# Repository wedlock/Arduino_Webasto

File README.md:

# Arduino_Webasto

Projekt sterownika do Webasto oparty na adruino ( w tym przyopadku Adruino nano ). Do działania całości niezbędne są dwa termometry ( DS18B20 ) do odczytu temperatury spalin i cieczy w układzie oraz wyświetlacz LCD 2x16 linii , 1 przycisk monostabilny, kilka rezystorów, MOSFETY i diody LED  ( wszystkie elementy są wymienione w schemacie ). Sterownik ustawiony jest na maksymalną temperaturę 70 stopni .

Do projektu dołączam pliki EAGLE i PDF niezbędne do wykonania płytki.

Krótka instrukcja działania :

Gdy sterownik znajduje się w stanie IDLE jednoktorne wciśnięcie przycisku powoduje rozpoczęcie sekwencji startowej. Na ekranie wyświetla się napis BURNING UP. Ponowne wciśnięcie przycisku w każdym momencie gdy sterownik jest w trybie BURNING UP, WORKING albo SLEEP powoduje wygaszenie pieca. Przytrzymanie przycisku 2 sek powoduje natychmiastowe zatrzymanie i reset programu.

Podczas pracy sterownik cały czas sprawdza temp. spalin i wody i gdy wykryje nieprawidłowości wyłącza układ. Mi osobiście przez całą zimę nie wyłączył się awaryjnie ani razu. Dla bezpieczeństwa wbudowałem watchdoga, który co kilka milisekund sprawdza czy arduino się zawiesiło, a jeśli tak to resetuje cału układ i wygasza się on bezpiecznie.

Stany sterownika:
1. IDLE oczekuje na włączenie ( sprawdzanie temp. cieczy ciągle włączone i ewentualnie włączy się pompa wody gdy temperatura wzrośnie )
2. BURNING UP rozpalanie pieca. Odbywa się to etapami :
  - przedmuchanie komory spalania celem pozbycia się oparów ropy
  - którkie pomowanie paliwa żeby rozsączyło się na palniku i odczekanie kulku sekund
  - włączenie świecy żarowej
  - gdy nastąpi wzrost temp. wody o 3 stopnie lub temp. wody o 2 stopnie piec przechodzi w tryb działania WORK
3. WORK - normalna praca pieca. Przy temp wody 20 stopni pompa wody jest włączana na 1/2 mocy. Zapobiega to gotowaniu się wody na powierzchni webasta. Po ogrzaniu się wody do 30 stopni sterownik urychamia się na 100% mocy. Gdy temp wody dojdzie do 70 stopni piec usypia się i czeka aż woda ostygnie do 65 stopni po czym znowy się uruchamia
4. BURN OFF wygaszanmie pieca. Nie jest podawane paliwa a wiatrak zwalnia. Zapobiega to cofaniu się płomienia. Gdy temp. spalin i wody przez dłuższą chwilę nie wzrasta, piec wyłącza się.

Na płytce zapomniałem dodać pinów do wlutowania przycisku ( ups. ) ale bez problemu da się to przylutować bezpośrednio do płytki. Są to przewody sygnałowe i ich średnica może być nawet i 0,5mm

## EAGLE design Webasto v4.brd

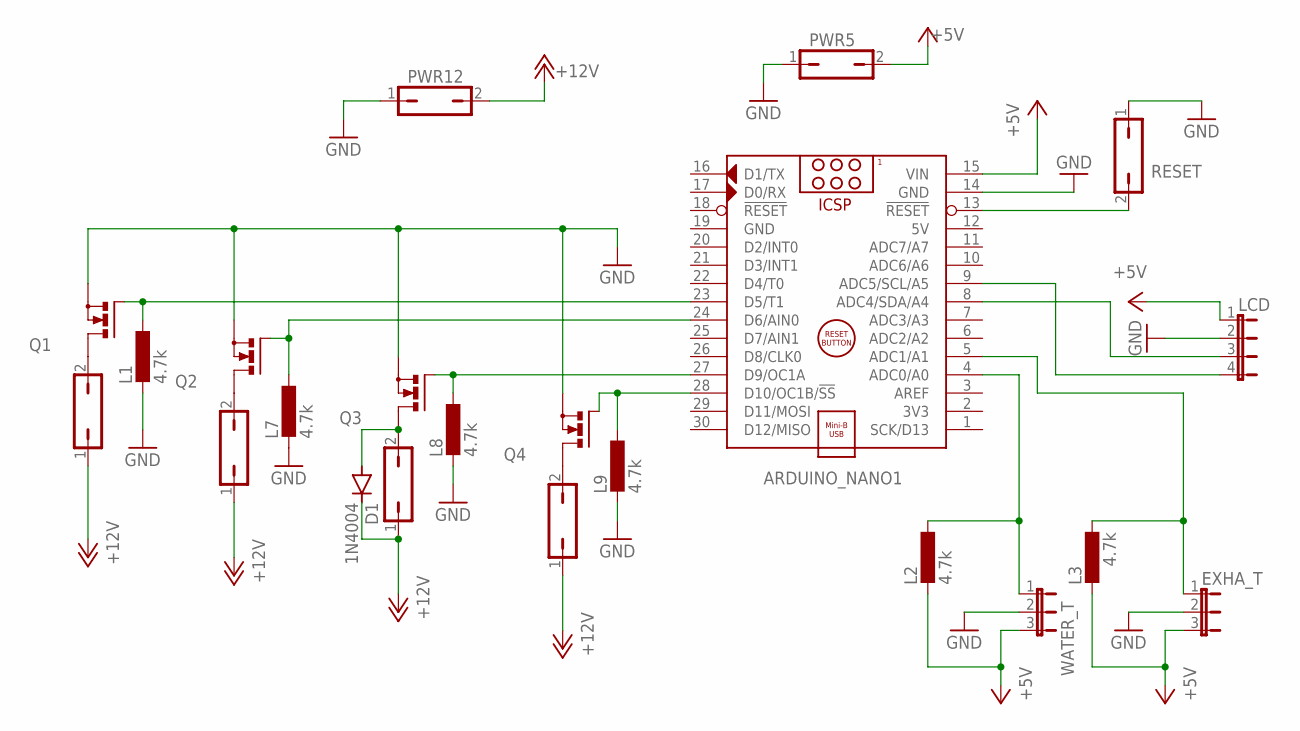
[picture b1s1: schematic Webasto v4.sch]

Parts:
ARDUINO_NANO1: ARDUINO_NANO
D1: 1N4004; DO41-10
EXHA_T: JP2E; JP2
FAN: 794681-2; JP1
FUEL: 794681-2; JP1
GLOW: 794681-2; JP1
L1, L2, L3, L7, L8, L9: 4.7k; 0204/7
LCD: JP4E; JP4
PWR5, PWR12: JP1Q; JP1
Q1, Q2, Q3, Q4: IRLB8721; TO220BV
RESET: power; JP1
WATER: 794681-2; JP1
WATER_T: JP2E; JP2

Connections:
5V: ARDUINO_NANO1.12 (5V)
+5V: ARDUINO_NANO1.15 (VIN), EXHA_T.3, L2.2, L3.2, LCD.1, PWR5.2, WATER_T.3
+12V: D1.C, FAN.1, FUEL.1, GLOW.1, PWR12.2, WATER.1
GND: ARDUINO_NANO1.14 (GND), ARDUINO_NANO1.19 (GND), EXHA_T.2, L1.2, L7.2, L8.2, L9.2, LCD.2, PWR5.1, PWR12.1, Q1.S, Q2.S, Q3.S, Q4.S, RESET.1, WATER_T.2
unnamed: ARDUINO_NANO1.23 (D5/T1), L1.1, Q1.G
unnamed: FUEL.2, Q1.D
unnamed: ARDUINO_NANO1.24 (D6/AIN0), L7.1, Q2.G
unnamed: GLOW.2, Q2.D
unnamed: ARDUINO_NANO1.27 (D9/OC1A), L8.1, Q3.G
unnamed: D1.A, FAN.2, Q3.D
unnamed: ARDUINO_NANO1.28 (D10/OC1B/!SS), L9.1, Q4.G
unnamed: Q4.D, WATER.2
unnamed: ARDUINO_NANO1.8 (ADC4/SDA/A4), LCD.3
unnamed: ARDUINO_NANO1.9 (ADC5/SCL/A5), LCD.4
unnamed: ARDUINO_NANO1.5 (ADC1/A1), EXHA_T.1, L3.1
unnamed: ARDUINO_NANO1.4 (ADC0/A0), L2.1, WATER_T.1
RESET: ARDUINO_NANO1.13 (!RESET), RESET.2

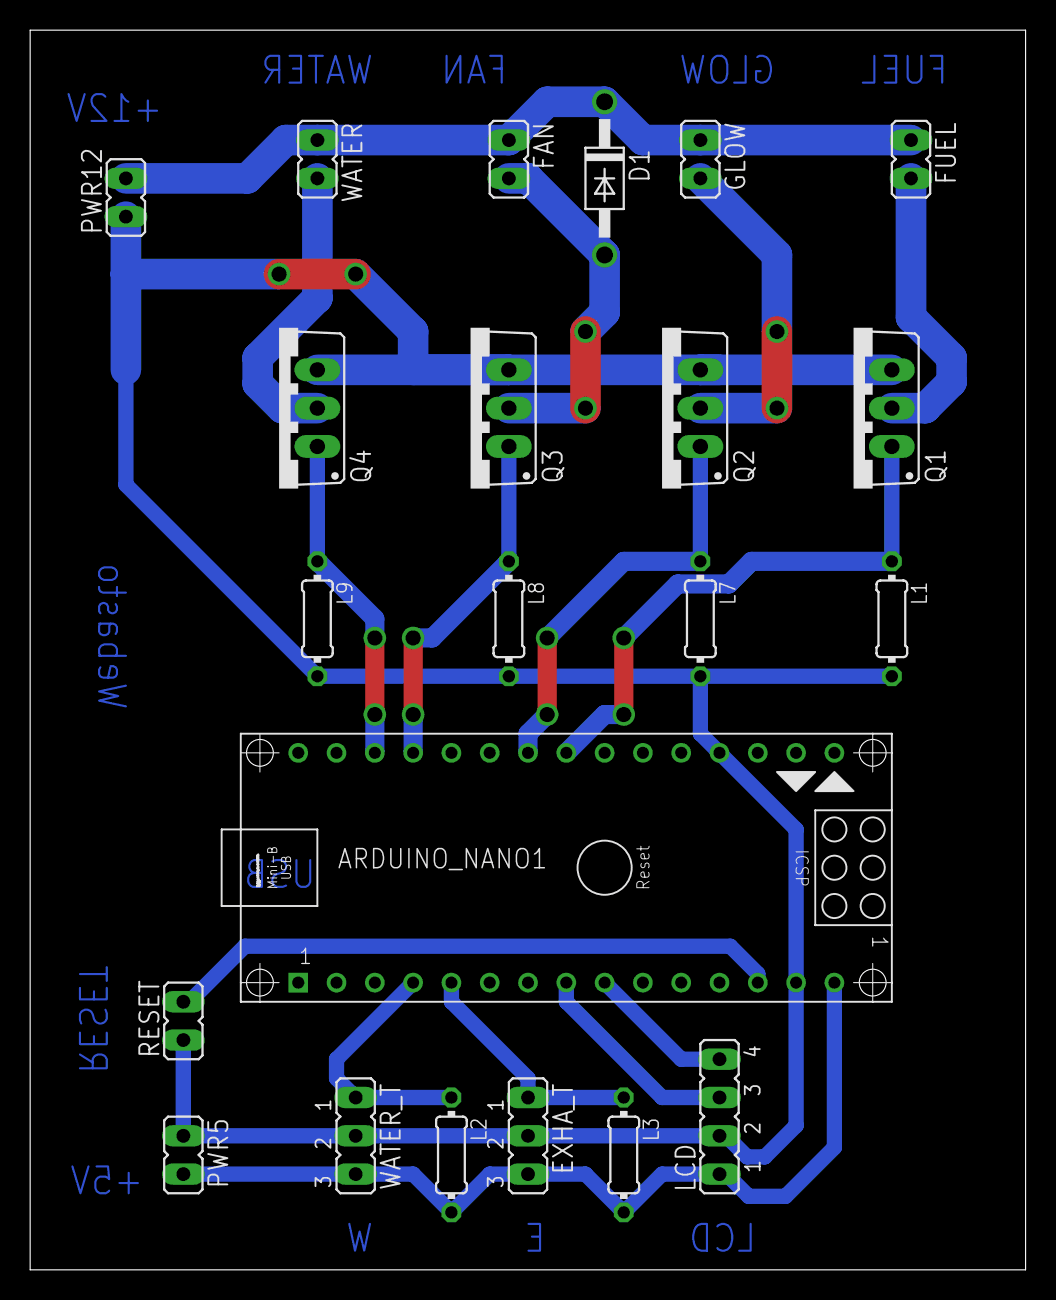
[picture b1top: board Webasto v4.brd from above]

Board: 2 copper layers, 66.0 x 82.2 mm, 22 parts (0 on the bottom side), 16 nets.
